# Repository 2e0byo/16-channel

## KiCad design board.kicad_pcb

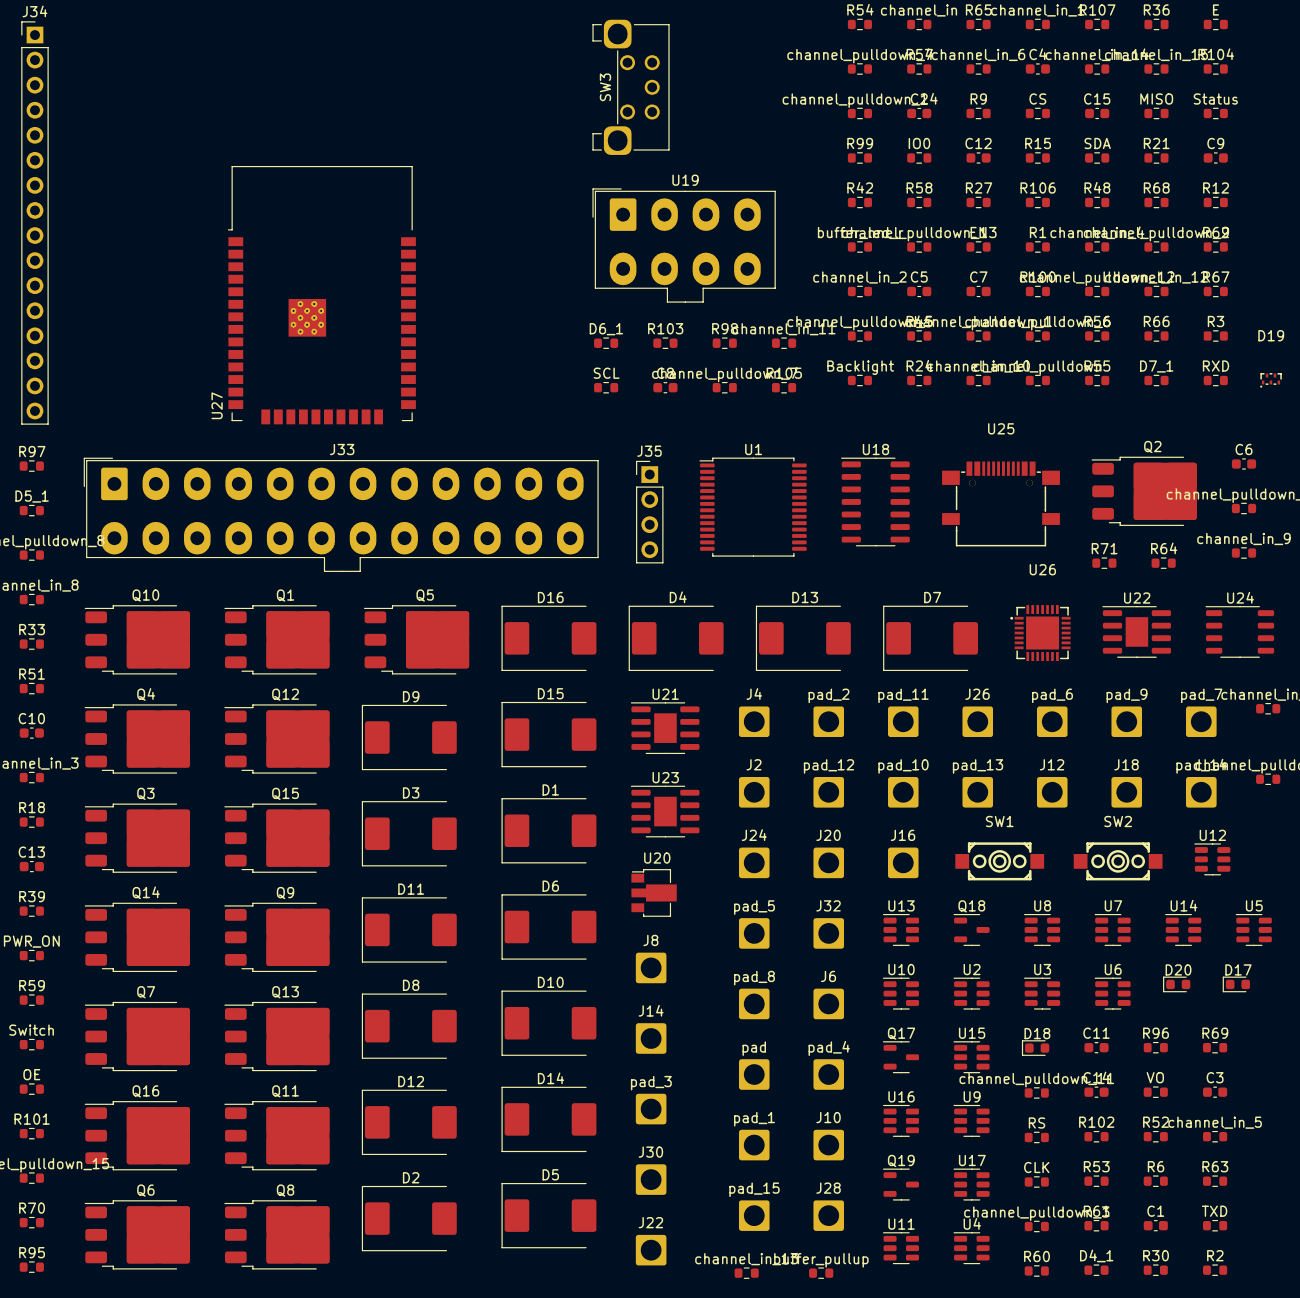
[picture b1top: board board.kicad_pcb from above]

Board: 2 copper layers, 226 parts (0 on the bottom side), 165 nets, no tracks yet.

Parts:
Backlight: 2K; R_0603_1608Metric
C1, C4, C5, C6, C7, C9, C10, C11, C14, C15: 100n; C_0603_1608Metric
C2, C3, C13: 22u; C_0603_1608Metric
C8: 1u; C_0603_1608Metric
C12: 4.7u; C_0603_1608Metric
CLK: 10R; R_0603_1608Metric
CS: 10R; R_0603_1608Metric
D1, D2, D3, D4, D5, D6, D7, D8, D9, D10, D11, D12, D13, D14, D15, D16: S5DC-13-F; D_SMC
D4_1, D5_1, D6_1, D7_1: 10R; R_0603_1608Metric
D17, D18, D20: LED; LED_0603_1608Metric
D19: RCLAMP7534P-N; DFN2010-5L_L2.0-W1.0-P0.8-BL
E: 10R; R_0603_1608Metric
EN: 10R; R_0603_1608Metric
IO0: 10R; R_0603_1608Metric
J2, J4, J6, J8, J10, J12, J14, J16, J18, J20, J22, J24, J26, J28, J30, J32: Conn_01x01; SolderWire-1.5sqmm_1x01_D1.7mm_OD3mm
J33: ATX-24; Molex_Mini-Fit_Jr_5566-24A_2x12_P4.20mm_Vertical
J34: Conn_01x16; PinHeader_1x16_P2.54mm_Vertical
J35: Conn_01x04_Male; PinHeader_1x04_P2.54mm_Vertical
MISO: 10R; R_0603_1608Metric
OE: 10R; R_0603_1608Metric
PWR_ON: 10R; R_0603_1608Metric
Q1, Q2, Q3, Q4, Q5, Q6, Q7, Q8, Q9, Q10, Q11, Q12, Q13, Q14, Q15, Q16: AOD508; TO-252-3_TabPin2
Q17, Q18, Q19: SS8050-G; SOT-23-3
R1, R2, R62, R98, R99, R100, R101, R102, R103, R104, R105, R106, R107: 10R; R_0603_1608Metric
R3, R6, R9, R12, R15, R18, R21, R24, R27, R30, R33, R36, R39, R42, R45, R48: 1R; R_0603_1608Metric
R51, R65: 2K; R_0603_1608Metric
R52: 220R; R_0603_1608Metric
R53: 1K; R_0603_1608Metric
R54, R55, R56: 100K; R_0603_1608Metric
R57, R58: 24K; R_0603_1608Metric
R59, R60: 30K; R_0603_1608Metric
R61: 12K; R_0603_1608Metric
R63, R64: 5K1; R_0603_1608Metric
R66: 22K1; R_0603_1608Metric
R67: 47K5; R_0603_1608Metric
R68, R69: 0; R_0603_1608Metric
R70, R71, R95: 10K; R_0603_1608Metric
R96, R97: 2K2; R_0603_1608Metric
RS: 10R; R_0603_1608Metric
RXD: 10R; R_0603_1608Metric
SCL: 10R; R_0603_1608Metric
SDA: 10R; R_0603_1608Metric
SW1, SW2: SW_Push; KEY-SMD_L6.2-W3.6-LS8.0
SW3: Rotary_Encoder_Switch; RotaryEncoder_Bourns_Horizontal_PEC12R-2xxxF-Sxxxx
Status: 2K; R_0603_1608Metric
Switch: 10R; R_0603_1608Metric
TXD: 10R; R_0603_1608Metric
U1: PCA9685PW; TSSOP-28_8x9.7mm_P0.65mm
U2, U3, U4, U5, U6, U7, U8, U9, U10, U11, U12, U13, U14, U15, U16, U17: ZXGD3001E6; SOT-23-6
U18: 74LS04; SOIC-14_3.9x8.7mm_P1.27mm
U19: EPS12V; Molex_Mini-Fit_Jr_5566-08A_2x04_P4.20mm_Vertical
U20: AP1117-15; SOT-89-3
U21: LM75AD; SOIC-8-1EP_3.9x4.9mm_P1.27mm_EP2.29x3mm
U22: ACS71240LLCBTR-030B3; SOIC-8-1EP_3.9x4.9mm_P1.27mm_EP2.29x3mm
U23: AP358SG-13; SOIC-8-1EP_3.9x4.9mm_P1.27mm_EP2.29x3mm
U24: MCP3201; SOP-8_3.9x4.9mm_P1.27mm
U25: YTC-TC16S-26; USB-C-SMD_YTC-TC16S-26-A
U26: CP2102N-A01-GQFN28; QFN-28_L5.0-W5.0-P0.50-TL-EP3.3
U27: ESP32-WROOM-32; ESP32-WROOM-32D
VO: 10R; R_0603_1608Metric
buffer_led_r: 2K; R_0603_1608Metric
buffer_pullup: 10K; R_0603_1608Metric
channel_in: 100R; R_0603_1608Metric
channel_in_1, channel_in_2, channel_in_3, channel_in_4, channel_in_5, channel_in_6, channel_in_7, channel_in_8, channel_in_9, channel_in_10, channel_in_11, channel_in_12, channel_in_13, channel_in_14, channel_in_15: 100R; R_0603_1608Metric
channel_pulldown: 100K; R_0603_1608Metric
channel_pulldown_1, channel_pulldown_2, channel_pulldown_3, channel_pulldown_4, channel_pulldown_5, channel_pulldown_6, channel_pulldown_7, channel_pulldown_8, channel_pulldown_9, channel_pulldown_10, channel_pulldown_11, channel_pulldown_12, channel_pulldown_13, channel_pulldown_14, channel_pulldown_15: 100K; R_0603_1608Metric
pad: Conn_01x01; SolderWire-1.5sqmm_1x01_D1.7mm_OD3mm
pad_1, pad_2, pad_3, pad_4, pad_5, pad_6, pad_7, pad_8, pad_9, pad_10, pad_11, pad_12, pad_13, pad_14, pad_15: Conn_01x01; SolderWire-1.5sqmm_1x01_D1.7mm_OD3mm

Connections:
+3V3: C3.1, C6.1, C7.1, C10.1, C11.1, C12.1, C13.1, C14.1, D17.1, J35.1, R51.1, R54.2, R55.2, R56.2, R57.1, R65.2, R96.2, R97.2, U18.14, U20.2, U21.8, U22.8, U24.1, U24.8, U26.6, U26.7, U27.2, buffer_pullup.1
+5V: C1.1, C2.1, C8.1, J33.9, J34.2, R52.2, U1.1, U1.3, U1.5, U1.28, U20.3, U23.8
Backlight: Backlight.2, R53.2
CLK: CLK.2, U24.7
CS: CS.2, U24.5
D4: D4_1.2, J34.11
D5: D5_1.2, J34.12
D6: D6_1.2, J34.13
D7: D7_1.2, J34.14
EN: C5.1, EN.2, Q18.3, SW2.2
GND: C1.2, C2.2, C3.2, C4.2, C5.2, C6.2, C7.2, C8.2, C9.2, C10.2, C11.2, C12.2, C13.2, C14.2, C15.1, C15.2, D18.2, D19.2, D20.2, E.2, EN.1, J33.3, J33.5, J33.7, J33.15, J33.17, J33.18, J33.19, J33.24, J34.1, J34.6, J35.2, Q1.3, Q2.3, Q3.3, Q4.3, Q5.3, Q6.3, Q7.3, Q8.3, Q9.3, Q10.3, Q11.3, Q12.3, Q13.3, Q14.3, Q15.3, Q16.3, Q17.2, R58.2, R60.2, R63.2, R64.2, R67.2, R95.1, R95.2, SW1.1, SW2.1, SW3.C, SW3.S2, Switch.2, U1.2, U1.4, U1.14, U1.24, U1.25, U2.3, U3.3, U4.3, U5.3, U6.3, U7.3, U8.3, U9.3, U10.3, U11.3, U12.3, U13.3, U14.3, U15.3, U16.3, U17.3, U18.5, U18.7, U18.9, U18.11, U18.13, U19.1, U19.2, U19.3, U19.4, U20.1, U21.4, U21.5, U21.6, U21.7, U22.5, U23.4, U23.5, U23.6, U24.3, U24.4, U25.12, U25.13, U25.14, U25.15, U25.A1B12, U25.A12B1, U26.3, U26.8, U26.29, U27.1, U27.3, U27.15, U27.38, U27.39, channel_pulldown.2, channel_pulldown_1.2, channel_pulldown_2.2, channel_pulldown_3.2, channel_pulldown_4.2, channel_pulldown_5.2, channel_pulldown_6.2, channel_pulldown_7.2, channel_pulldown_8.2, channel_pulldown_9.2, channel_pulldown_10.2, channel_pulldown_11.2, channel_pulldown_12.2, channel_pulldown_13.2, channel_pulldown_14.2, channel_pulldown_15.2
HV: D1.1, D2.1, D3.1, D4.1, D5.1, D6.1, D7.1, D8.1, D9.1, D10.1, D11.1, D12.1, D13.1, D14.1, D15.1, D16.1, U2.1, U3.1, U4.1, U5.1, U6.1, U7.1, U8.1, U9.1, U10.1, U11.1, U12.1, U13.1, U14.1, U15.1, U16.1, U17.1, U22.3, U22.4, pad.1, pad_1.1, pad_2.1, pad_3.1, pad_4.1, pad_5.1, pad_6.1, pad_7.1, pad_8.1, pad_9.1, pad_10.1, pad_11.1, pad_12.1, pad_13.1, pad_14.1, pad_15.1
HV_UPSTREAM: J33.10, J33.11, U19.5, U19.6, U19.7, U19.8, U22.1, U22.2
IO0: C4.1, IO0.2, Q19.3, SW1.2
MISO: MISO.2, U24.6
unnamed: U2.2, U2.5, channel_in.2
unnamed: R3.1, U2.4, U2.6
unnamed: D1.2, J2.1, Q1.2
unnamed: Q1.1, R3.2, channel_pulldown.1
unnamed: U3.2, U3.5, channel_in_1.2
unnamed: R6.1, U3.4, U3.6
unnamed: D2.2, J4.1, Q2.2
unnamed: Q2.1, R6.2, channel_pulldown_1.1
unnamed: U4.2, U4.5, channel_in_2.2
unnamed: R9.1, U4.4, U4.6
unnamed: D3.2, J6.1, Q3.2
unnamed: Q3.1, R9.2, channel_pulldown_2.1
unnamed: U5.2, U5.5, channel_in_3.2
unnamed: R12.1, U5.4, U5.6
unnamed: D4.2, J8.1, Q4.2
unnamed: Q4.1, R12.2, channel_pulldown_3.1
unnamed: U6.2, U6.5, channel_in_4.2
unnamed: R15.1, U6.4, U6.6
unnamed: D5.2, J10.1, Q5.2
unnamed: Q5.1, R15.2, channel_pulldown_4.1
unnamed: U7.2, U7.5, channel_in_5.2
unnamed: R18.1, U7.4, U7.6
unnamed: D6.2, J12.1, Q6.2
unnamed: Q6.1, R18.2, channel_pulldown_5.1
unnamed: U8.2, U8.5, channel_in_6.2
unnamed: R21.1, U8.4, U8.6
unnamed: D7.2, J14.1, Q7.2
unnamed: Q7.1, R21.2, channel_pulldown_6.1
unnamed: U9.2, U9.5, channel_in_7.2
unnamed: R24.1, U9.4, U9.6
unnamed: D8.2, J16.1, Q8.2
unnamed: Q8.1, R24.2, channel_pulldown_7.1
unnamed: U10.2, U10.5, channel_in_8.2
unnamed: R27.1, U10.4, U10.6
unnamed: D9.2, J18.1, Q9.2
unnamed: Q9.1, R27.2, channel_pulldown_8.1
unnamed: U11.2, U11.5, channel_in_9.2
unnamed: R30.1, U11.4, U11.6
unnamed: D10.2, J20.1, Q10.2
unnamed: Q10.1, R30.2, channel_pulldown_9.1
unnamed: U12.2, U12.5, channel_in_10.2
unnamed: R33.1, U12.4, U12.6
unnamed: D11.2, J22.1, Q11.2
unnamed: Q11.1, R33.2, channel_pulldown_10.1
unnamed: U13.2, U13.5, channel_in_11.2
unnamed: R36.1, U13.4, U13.6
unnamed: D12.2, J24.1, Q12.2
unnamed: Q12.1, R36.2, channel_pulldown_11.1
unnamed: U14.2, U14.5, channel_in_12.2
unnamed: R39.1, U14.4, U14.6
unnamed: D13.2, J26.1, Q13.2
unnamed: Q13.1, R39.2, channel_pulldown_12.1
unnamed: U15.2, U15.5, channel_in_13.2
unnamed: R42.1, U15.4, U15.6
unnamed: D14.2, J28.1, Q14.2
unnamed: Q14.1, R42.2, channel_pulldown_13.1
unnamed: U16.2, U16.5, channel_in_14.2
unnamed: R45.1, U16.4, U16.6
unnamed: D15.2, J30.1, Q15.2
unnamed: Q15.1, R45.2, channel_pulldown_14.1
unnamed: U17.2, U17.5, channel_in_15.2
unnamed: R48.1, U17.4, U17.6
unnamed: D16.2, J32.1, Q16.2
unnamed: Q16.1, R48.2, channel_pulldown_15.1
unnamed: U1.6, channel_in.1
unnamed: U1.7, channel_in_1.1
unnamed: U1.8, channel_in_2.1
unnamed: U1.9, channel_in_3.1
unnamed: U1.10, channel_in_4.1
unnamed: U1.11, channel_in_5.1
unnamed: U1.12, channel_in_6.1
unnamed: U1.13, channel_in_7.1
unnamed: U1.15, channel_in_8.1
unnamed: U1.16, channel_in_9.1
unnamed: U1.17, channel_in_10.1
unnamed: U1.18, channel_in_11.1
unnamed: U1.19, channel_in_12.1
unnamed: U1.20, channel_in_13.1
unnamed: U1.21, channel_in_14.1
unnamed: U1.22, channel_in_15.1
unnamed: D17.2, buffer_led_r.1
unnamed: U18.4, buffer_led_r.2
unnamed: D18.1, R51.2
unnamed: J34.15, R52.1
unnamed: J34.16, Q17.3
unnamed: Q17.1, R53.1
unnamed: R56.1, SW3.S1
unnamed: R57.2, R58.1, R59.2, U23.2
unnamed: R59.1, R62.2, U23.1
unnamed: C9.1, R60.1, R61.1, U23.3
unnamed: R61.2, U22.7
unnamed: R62.1, U24.2
unnamed: R63.1, U25.A5
unnamed: R64.1, U25.B5
unnamed: D19.5, U25.A6, U25.B6, U26.4
unnamed: D19.4, U25.A7, U25.B7, U26.5
unnamed: D19.1, R66.1, U25.A4B9, U25.A9B4
unnamed: R65.1, U26.9
unnamed: R66.2, R67.1
unnamed: R68.1, U26.26
unnamed: R69.1, U26.25
unnamed: Q18.1, R70.1
unnamed: Q19.2, R70.2, U26.28
unnamed: Q18.2, R71.2, U26.24
unnamed: Q19.1, R71.1
unnamed: U27.8, VO.1
unnamed: RS.1, U27.9
unnamed: E.1, U27.10
unnamed: D4_1.1, U27.11
unnamed: D5_1.1, U27.12
unnamed: D6_1.1, U27.13
unnamed: D7_1.1, U27.16
unnamed: Backlight.1, U27.26
unnamed: SDA.1, U27.36
unnamed: SCL.1, U27.33
unnamed: OE.1, U27.37
unnamed: PWR_ON.1, U27.27
unnamed: TXD.1, U27.35
unnamed: RXD.1, U27.34
unnamed: IO0.1, U27.25
unnamed: R1.1, U27.6
unnamed: R2.1, U27.7
unnamed: Switch.1, U27.4
unnamed: MISO.1, U27.30
unnamed: CLK.1, U27.29
unnamed: CS.1, U27.28
unnamed: Status.1, U27.24
unnamed: D20.1, Status.2
unnamed: R98.1, U27.14
unnamed: R99.1, U27.17
unnamed: R100.1, U27.18
unnamed: R101.1, U27.19
unnamed: R102.1, U27.20
unnamed: R103.1, U27.21
unnamed: R104.1, U27.22
unnamed: R105.1, U27.23
unnamed: R106.1, U27.31
unnamed: R107.1, U27.5
OE: OE.2, U21.3, U22.6
OE_1: U18.1, U18.3, buffer_pullup.2
PWR_ON: J33.16, PWR_ON.2
R1: R1.2, R55.1, SW3.A
R2: R2.2, R54.1, SW3.B
RS: J34.4, RS.2
RXD: R69.2, RXD.2
SCL: J35.4, R97.1, SCL.2, U1.26, U21.2
SDA: J35.3, R96.1, SDA.2, U1.27, U21.1
TXD: R68.2, TXD.2
VO: J34.3, VO.2
~OE: U1.23, U18.2

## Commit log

2023-05-14 feat: schem passing erc, needing footprints.
2023-05-15 feat: all footprints.
2023-05-15 fix: use easyeda footprint.
2023-05-15 chore: cleanup poetry.
2023-05-15 feat: design through to pcb.
2023-05-15 feat: start pcb.
2023-07-01 refactor: move hal to firmware and make static form for mcu.
2023-07-01 feat: interface.
2023-07-01 dev: makefile.
2023-07-01 chore: ignore mirror dir used by makefile to deploy.
2023-07-02 feat: pca9685.
2023-07-02 feat: jsonrpc.
2023-07-09 chore: ignore env file.
2023-07-09 fix: fixups for pca6985.
2023-07-09 dev: install jsonrpc.
2023-07-09 feat: main.
2023-07-09 feat: network.
2023-07-09 dev: install conn, env and by webrepl.
    Yes, that's a committed password. Webrepl isn't secure anyway; it shouldn't be
    on in prod.
2023-07-09 fix(rpc): handle no params.
2023-07-09 feat: serial json-rpc.
2023-07-11 feat: configurable wifi.
